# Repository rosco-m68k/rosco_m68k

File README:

# Motorola 68k single-board computer

This repository holds design files, firmware and software for my m68k 
single-board computer, AKA the Rosco_m68k.

You can find the project along with some logs about its development
on Hackaday: https://hackaday.io/project/164305-yet-another-m68k-homebrew

All released under the MIT licence. See LICENSE for details.

## Current design

Currently, the design for the system is:

* MC68010P10 at 8MHz, /DTACK grounded
* 16KB IO Space (0xF80000 - 0xFEFFFF)
* 16KB ROM (at 0xFC0000)
* 1MB RAM (0x0 - 0xFFFFF)
* TTL-based address decoding

In terms of software:

* Simple code in ROM to do various tests etc.
* Built with GCC and VASM

## Next steps

* Integrate MC68901 MFP
** This will provide timers, and a UART we can use to hook up a terminal. It also has some GPIOs and does interrupt handling (I already have the IC).
* Graphics - I'm thinking maybe Yamaha V9958 (assuming I can get hold of one)
** I would have liked to have used a Denise, but that would probably also require a (non-breadboard-friendly) Agnus.
** The datasheet and manual for the Denise probably aren't as easy to come by or complete, so there'd be more reverse-engineering.
* OS - Once the timers are available and I have some I/O capability, I want to build out the OS.
** Microkernel architecture (Similar in principle to Exec)
** Preemptive multitasking
** External storage (probably CF or SD in the first instance, though SD would require level shifting).

## Ideas for future enhancement

### Minimal memory protection

Extend address decoder to disallow access to certain locations based on 68k function pins.
E.g. in user mode:

	* Disallow ROM
	* Disallow IO
	* Disallow xKB at bottom of RAM (ExVecs and kernel heap)

The last one would make null dereferences generate a bus error.

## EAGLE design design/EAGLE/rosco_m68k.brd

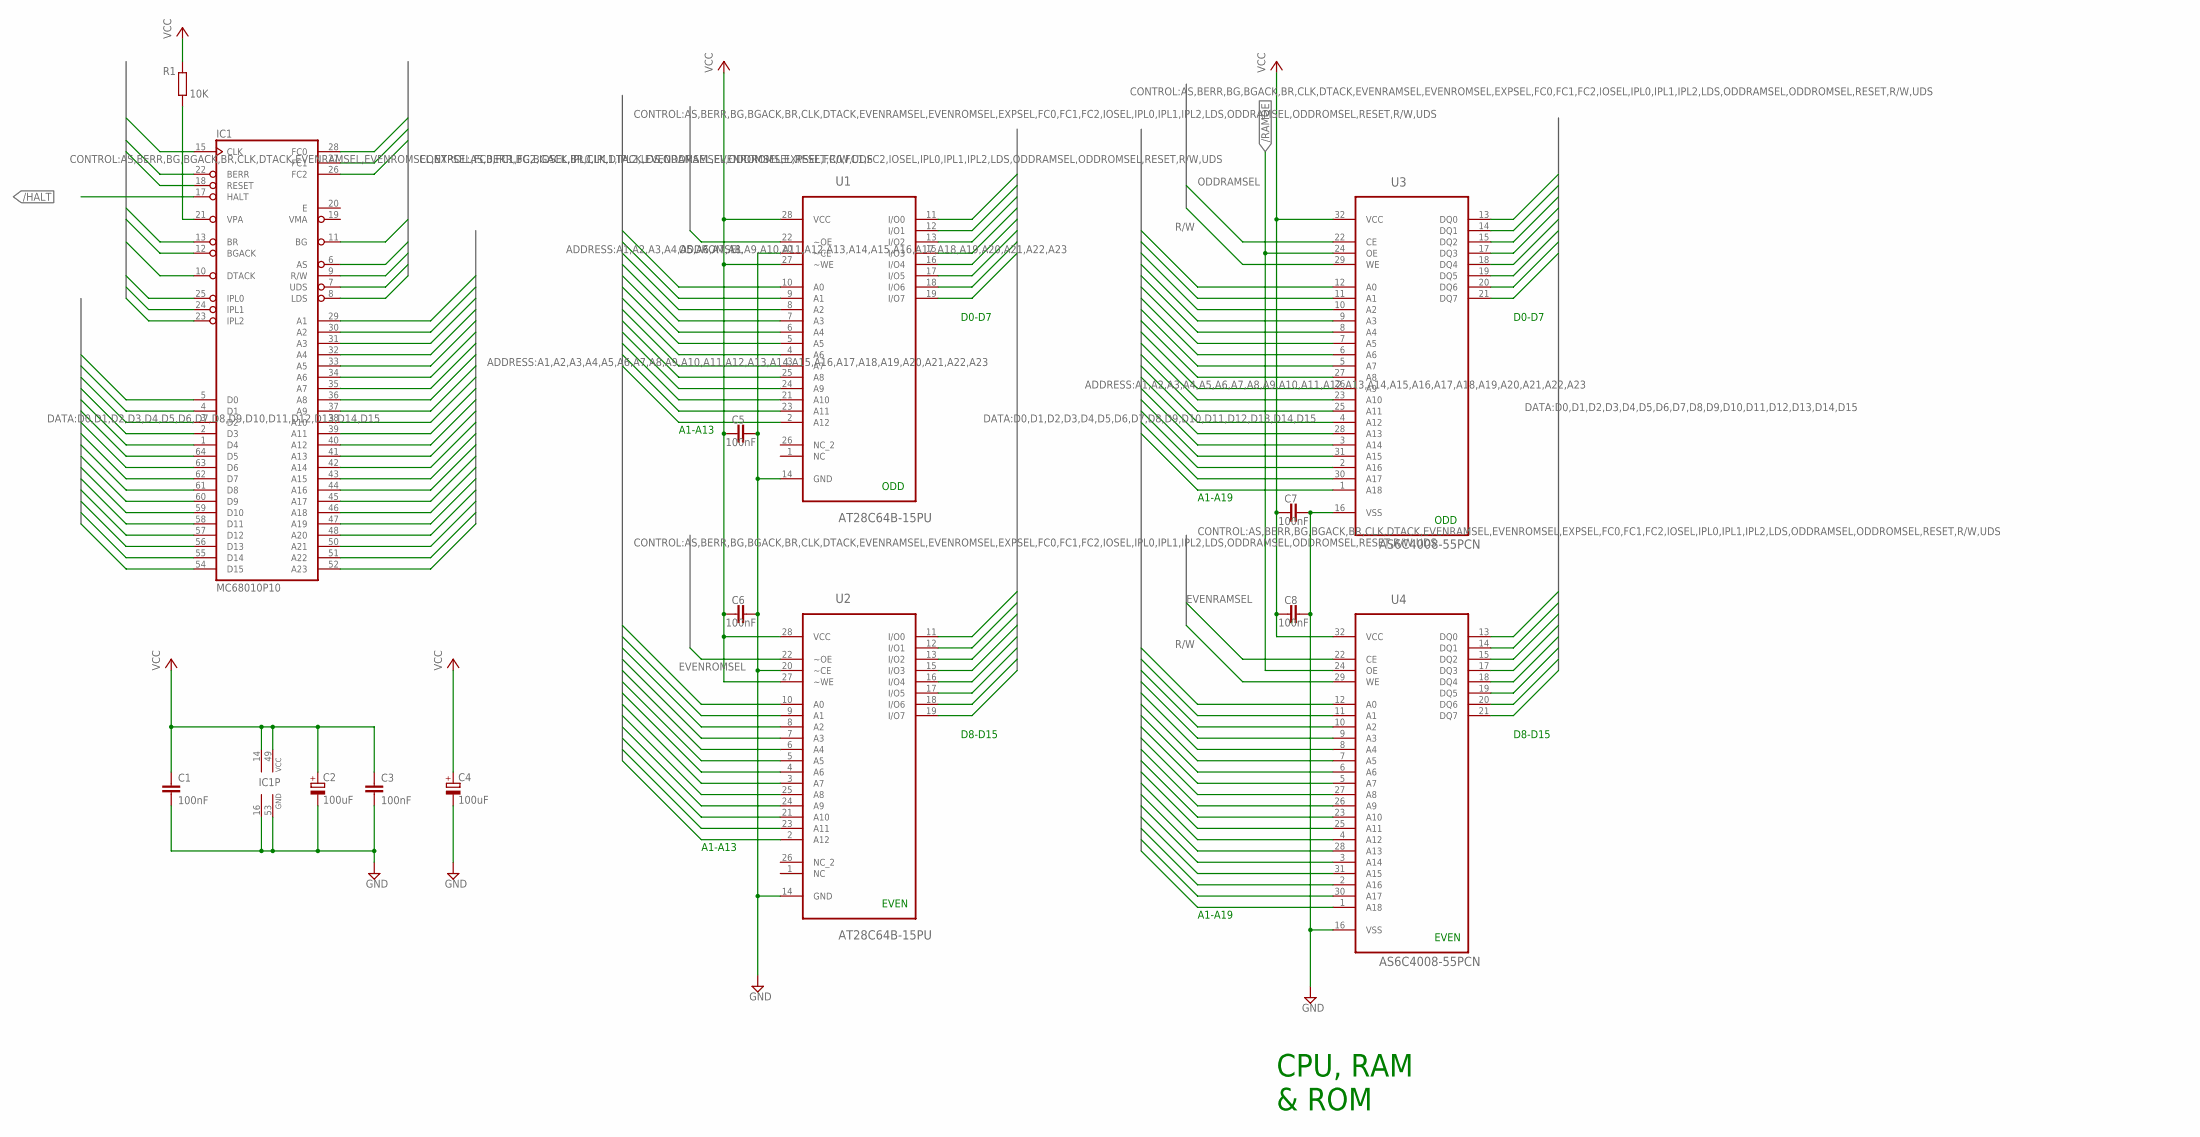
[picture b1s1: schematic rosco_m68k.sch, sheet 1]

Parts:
C1, C3, C5, C6, C7, C8: 100nF; C2.5-3
C2, C4: 100uF; E2,5-5
IC1: MC68010P10; DIL64
R1: 10K; 0207/10
U1, U2: AT28C64B-15PU; DIP254P1524X482-28
U3, U4: AS6C4008-55PCN; DIP254P1524X393-32

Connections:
/HALT: IC1.17 (HALT); also elsewhere on the board
/RAMOE: U3.24 (OE), U4.24 (OE); also elsewhere on the board
A1: IC1.29 (A1), U1.10 (A0), U2.10 (A0), U3.12 (A0), U4.12 (A0); also elsewhere on the board
A2: IC1.30 (A2), U1.9 (A1), U2.9 (A1), U3.11 (A1), U4.11 (A1); also elsewhere on the board
A3: IC1.31 (A3), U1.8 (A2), U2.8 (A2), U3.10 (A2), U4.10 (A2); also elsewhere on the board
A4: IC1.32 (A4), U1.7 (A3), U2.7 (A3), U3.9 (A3), U4.9 (A3); also elsewhere on the board
A5: IC1.33 (A5), U1.6 (A4), U2.6 (A4), U3.8 (A4), U4.8 (A4); also elsewhere on the board
A6: IC1.34 (A6), U1.5 (A5), U2.5 (A5), U3.7 (A5), U4.7 (A5); also elsewhere on the board
A7: IC1.35 (A7), U1.4 (A6), U2.4 (A6), U3.6 (A6), U4.6 (A6); also elsewhere on the board
A8: IC1.36 (A8), U1.3 (A7), U2.3 (A7), U3.5 (A7), U4.5 (A7); also elsewhere on the board
A9: IC1.37 (A9), U1.25 (A8), U2.25 (A8), U3.27 (A8), U4.27 (A8); also elsewhere on the board
A10: IC1.38 (A10), U1.24 (A9), U2.24 (A9), U3.26 (A9), U4.26 (A9); also elsewhere on the board
A11: IC1.39 (A11), U1.21 (A10), U2.21 (A10), U3.23 (A10), U4.23 (A10); also elsewhere on the board
A12: IC1.40 (A12), U1.23 (A11), U2.23 (A11), U3.25 (A11), U4.25 (A11); also elsewhere on the board
A13: IC1.41 (A13), U1.2 (A12), U2.2 (A12), U3.4 (A12), U4.4 (A12); also elsewhere on the board
A14: IC1.42 (A14), U3.28 (A13), U4.28 (A13); also elsewhere on the board
A15: IC1.43 (A15), U3.3 (A14), U4.3 (A14); also elsewhere on the board
A16: IC1.44 (A16), U3.31 (A15), U4.31 (A15); also elsewhere on the board
A17: IC1.45 (A17), U3.2 (A16), U4.2 (A16); also elsewhere on the board
A18: IC1.46 (A18), U3.30 (A17), U4.30 (A17); also elsewhere on the board
A19: IC1.47 (A19), U3.1 (A18), U4.1 (A18); also elsewhere on the board
A20: IC1.48 (A20); also elsewhere on the board
A21: IC1.50 (A21); also elsewhere on the board
A22: IC1.51 (A22); also elsewhere on the board
A23: IC1.52 (A23); also elsewhere on the board
AS: IC1.6 (AS); also elsewhere on the board
BERR: IC1.22 (BERR); also elsewhere on the board
BG: IC1.11 (BG); also elsewhere on the board
BGACK: IC1.12 (BGACK); also elsewhere on the board
BR: IC1.13 (BR); also elsewhere on the board
CLK: IC1.15 (CLK); also elsewhere on the board
D0: IC1.5 (D0), U1.11 (I/O0), U3.13 (DQ0); also elsewhere on the board
D1: IC1.4 (D1), U1.12 (I/O1), U3.14 (DQ1); also elsewhere on the board
D2: IC1.3 (D2), U1.13 (I/O2), U3.15 (DQ2); also elsewhere on the board
D3: IC1.2 (D3), U1.15 (I/O3), U3.17 (DQ3); also elsewhere on the board
D4: IC1.1 (D4), U1.16 (I/O4), U3.18 (DQ4); also elsewhere on the board
D5: IC1.64 (D5), U1.17 (I/O5), U3.19 (DQ5); also elsewhere on the board
D6: IC1.63 (D6), U1.18 (I/O6), U3.20 (DQ6); also elsewhere on the board
D7: IC1.62 (D7), U1.19 (I/O7), U3.21 (DQ7); also elsewhere on the board
D8: IC1.61 (D8), U2.11 (I/O0), U4.13 (DQ0); also elsewhere on the board
D9: IC1.60 (D9), U2.12 (I/O1), U4.14 (DQ1); also elsewhere on the board
D10: IC1.59 (D10), U2.13 (I/O2), U4.15 (DQ2); also elsewhere on the board
D11: IC1.58 (D11), U2.15 (I/O3), U4.17 (DQ3); also elsewhere on the board
D12: IC1.57 (D12), U2.16 (I/O4), U4.18 (DQ4); also elsewhere on the board
D13: IC1.56 (D13), U2.17 (I/O5), U4.19 (DQ5); also elsewhere on the board
D14: IC1.55 (D14), U2.18 (I/O6), U4.20 (DQ6); also elsewhere on the board
D15: IC1.54 (D15), U2.19 (I/O7), U4.21 (DQ7); also elsewhere on the board
DTACK: IC1.10 (DTACK); also elsewhere on the board
EVENRAMSEL: U4.22 (CE); also elsewhere on the board
EVENROMSEL: U2.22 (~OE); also elsewhere on the board
FC0: IC1.28 (FC0); also elsewhere on the board
FC1: IC1.27 (FC1); also elsewhere on the board
FC2: IC1.26 (FC2); also elsewhere on the board
GND: C1.2, C2.-, C3.2, C4.-, C5.2, C6.2, C7.2, C8.2, IC1.16 (GND), IC1.53 (GND), U1.14 (GND), U1.20 (~CE), U2.14 (GND), U2.20 (~CE), U3.16 (VSS), U4.16 (VSS); also elsewhere on the board
IPL0: IC1.25 (IPL0); also elsewhere on the board
IPL1: IC1.24 (IPL1); also elsewhere on the board
IPL2: IC1.23 (IPL2); also elsewhere on the board
LDS: IC1.8 (LDS); also elsewhere on the board
ODDRAMSEL: U3.22 (CE); also elsewhere on the board
ODDROMSEL: U1.22 (~OE); also elsewhere on the board
R/W: IC1.9 (R/W), U3.29 (WE), U4.29 (WE); also elsewhere on the board
RESET: IC1.18 (RESET); also elsewhere on the board
UDS: IC1.7 (UDS); also elsewhere on the board
VCC: C1.1, C2.+, C3.1, C4.+, C5.1, C6.1, C7.1, C8.1, IC1.14 (VCC), IC1.49 (VCC), R1.2, U1.27 (~WE), U1.28 (VCC), U2.27 (~WE), U2.28 (VCC), U3.32 (VCC), U4.32 (VCC); also elsewhere on the board
VPA: IC1.21 (VPA), R1.1

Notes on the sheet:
ODD
EVEN
D0-D7
D8-D15
A1-A13
A1-A19
CPU, RAM & ROM

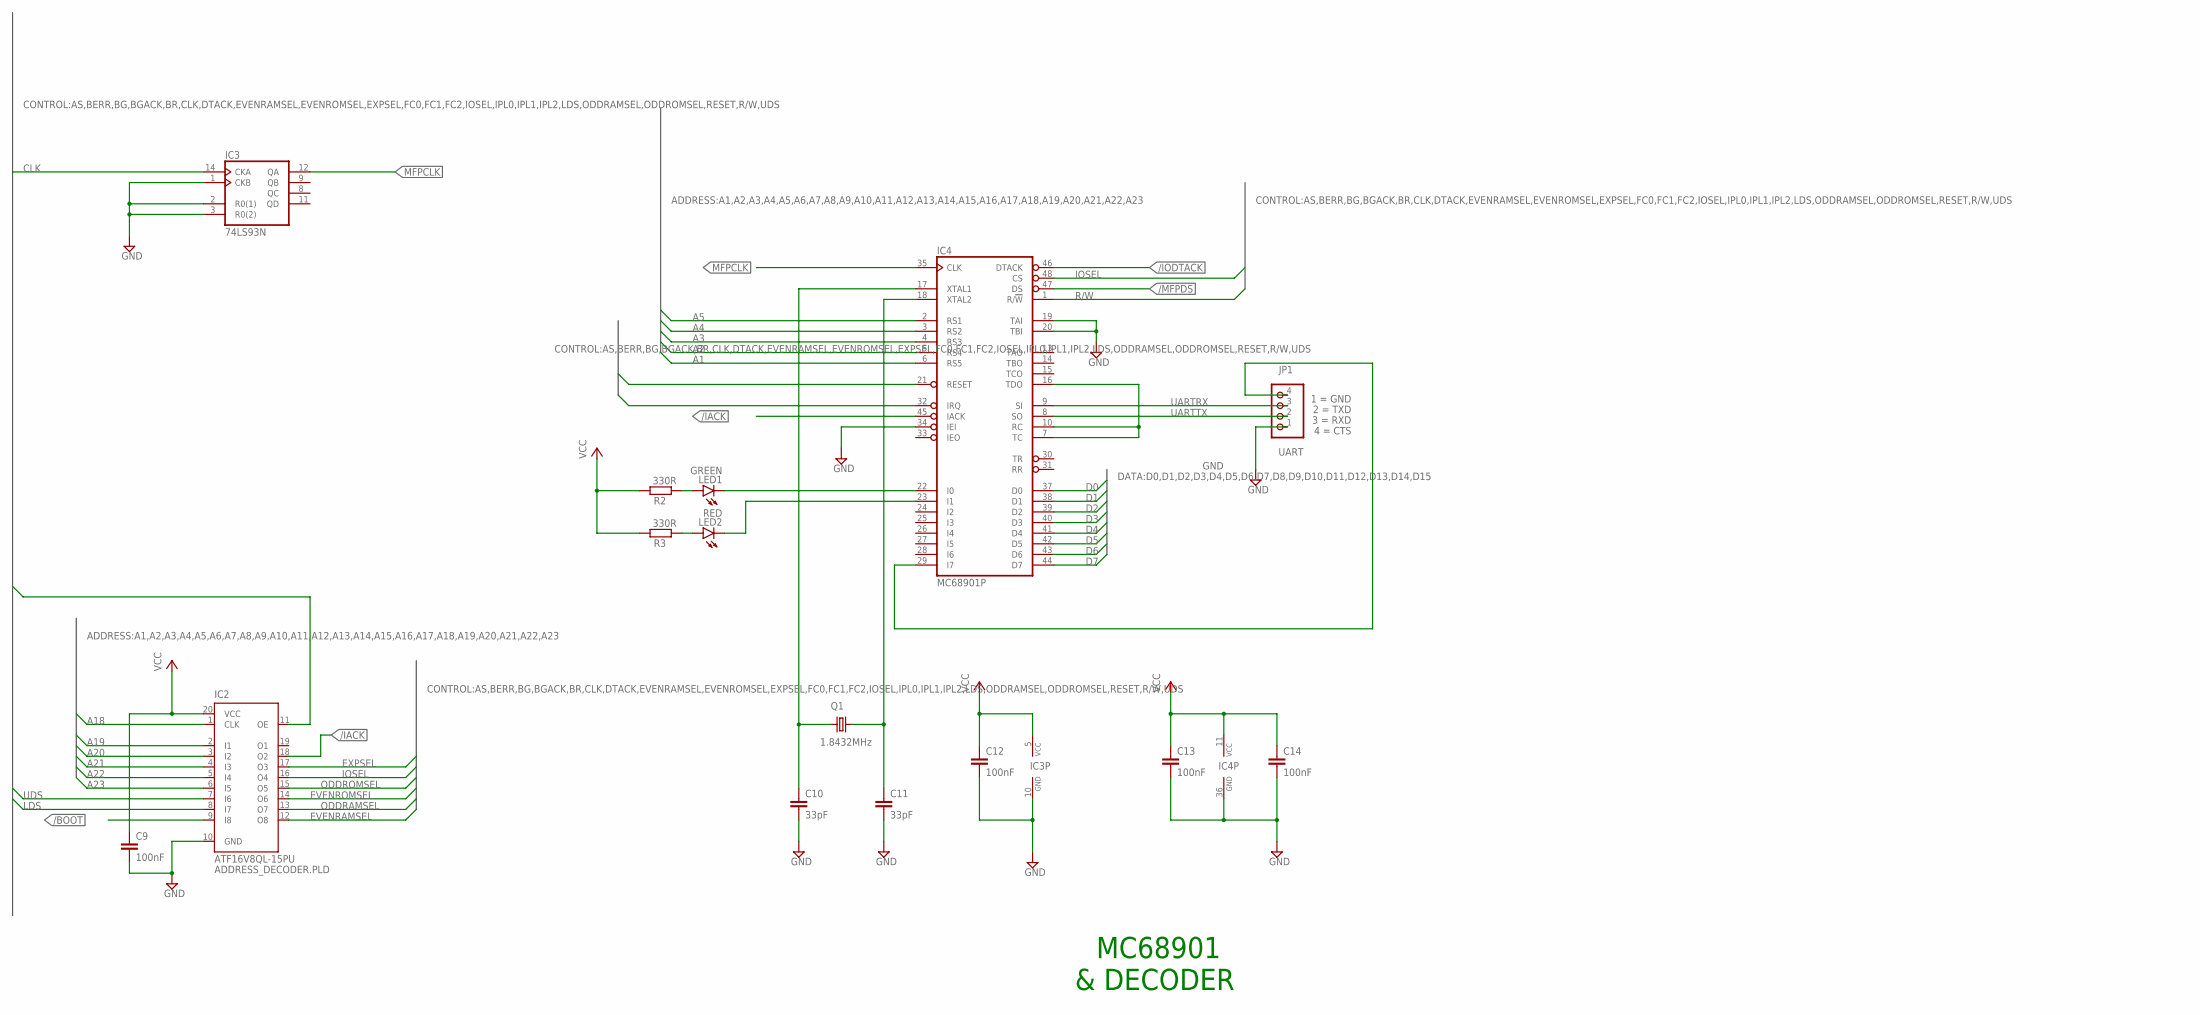
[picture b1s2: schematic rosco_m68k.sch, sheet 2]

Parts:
C9, C12, C13, C14: 100nF; C2.5-3
C10, C11: 33pF; C2.5-3
IC2: ATF16V8QL-15PU; DIL20; MPN ATF16V8QL-15PU
IC3: 74LS93N; DIL14
IC4: MC68901P; DIL48
JP1: UART; 1X04
LED1: GREEN; LED5MM
LED2: RED; LED5MM
Q1: 1.8432MHz; HC49/S
R2, R3: 330R; 0207/10

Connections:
/BOOT: IC2.9 (I8); also elsewhere on the board
/IACK: IC2.18 (O2), IC4.45 (IACK); also elsewhere on the board
/IODTACK: IC4.46 (DTACK); also elsewhere on the board
/MFPDS: IC4.47 (DS); also elsewhere on the board
A1: IC4.6 (RS5); also elsewhere on the board
A2: IC4.5 (RS4); also elsewhere on the board
A3: IC4.4 (RS3); also elsewhere on the board
A4: IC4.3 (RS2); also elsewhere on the board
A5: IC4.2 (RS1); also elsewhere on the board
A18: IC2.1 (CLK); also elsewhere on the board
A19: IC2.2 (I1); also elsewhere on the board
A20: IC2.3 (I2); also elsewhere on the board
A21: IC2.4 (I3); also elsewhere on the board
A22: IC2.5 (I4); also elsewhere on the board
A23: IC2.6 (I5); also elsewhere on the board
AS: IC2.11 (OE); also elsewhere on the board
CLK: IC3.14 (CKA); also elsewhere on the board
D0: IC4.37 (D0); also elsewhere on the board
D1: IC4.38 (D1); also elsewhere on the board
D2: IC4.39 (D2); also elsewhere on the board
D3: IC4.40 (D3); also elsewhere on the board
D4: IC4.41 (D4); also elsewhere on the board
D5: IC4.42 (D5); also elsewhere on the board
D6: IC4.43 (D6); also elsewhere on the board
D7: IC4.44 (D7); also elsewhere on the board
EVENRAMSEL: IC2.12 (O8); also elsewhere on the board
EVENROMSEL: IC2.14 (O6); also elsewhere on the board
EXPSEL: IC2.17 (O3); also elsewhere on the board
GND: C9.2, C10.2, C11.2, C12.2, C13.2, C14.2, IC2.10 (GND), IC3.1 (CKB), IC3.2 (R0(1)), IC3.3 (R0(2)), IC3.10 (GND), IC4.19 (TAI), IC4.20 (TBI), IC4.34 (IEI), IC4.36 (GND), JP1.1; also elsewhere on the board
IOSEL: IC2.16 (O4), IC4.48 (CS); also elsewhere on the board
IPL2: IC4.32 (IRQ); also elsewhere on the board
LDS: IC2.8 (I7); also elsewhere on the board
MFPCLK: IC3.12 (QA), IC4.35 (CLK)
MFPIO0: IC4.22 (I0), LED1.K (C)
MFPIO1: IC4.23 (I1), LED2.K (C)
MFPXTAL1: C10.1, IC4.17 (XTAL1), Q1.1
MFPXTAL2: C11.1, IC4.18 (XTAL2), Q1.2
unnamed: LED2.A, R3.1
unnamed: LED1.A, R2.1
ODDRAMSEL: IC2.13 (O7); also elsewhere on the board
ODDROMSEL: IC2.15 (O5); also elsewhere on the board
R/W: IC4.1 (R/!W); also elsewhere on the board
RESET: IC4.21 (RESET); also elsewhere on the board
UARTCLK: IC4.7 (TC), IC4.10 (RC), IC4.16 (TDO)
UARTCTS: IC4.29 (I7), JP1.4
UARTRX: IC4.9 (SI), JP1.3
UARTTX: IC4.8 (SO), JP1.2
UDS: IC2.7 (I6); also elsewhere on the board
VCC: C9.1, C12.1, C13.1, C14.1, IC2.20 (VCC), IC3.5 (VCC), IC4.11 (VCC), R2.2, R3.2; also elsewhere on the board

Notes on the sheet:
MC68901
& DECODER

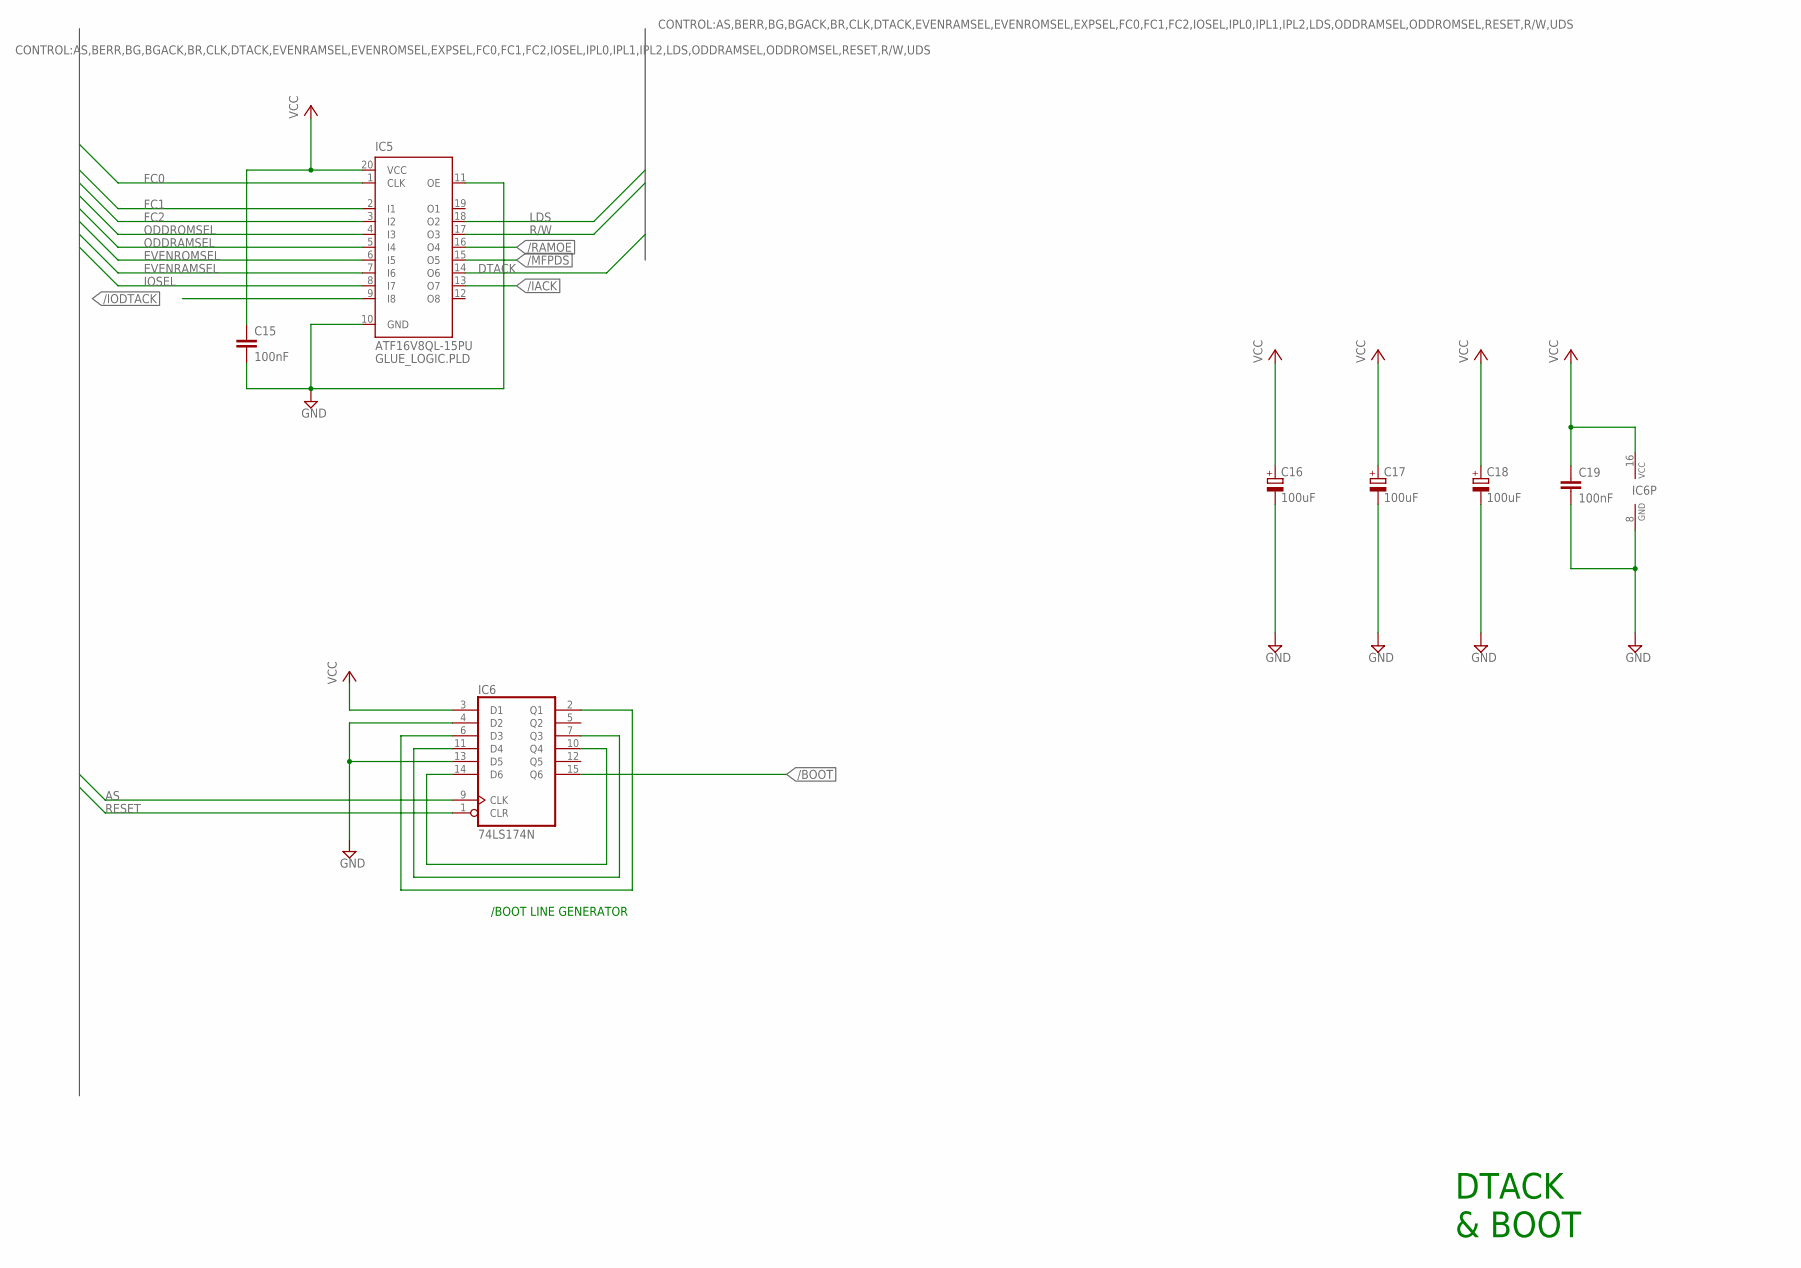
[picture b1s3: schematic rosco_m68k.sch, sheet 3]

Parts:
C15, C19: 100nF; C2.5-3
C16, C17, C18: 100uF; E2,5-5
IC5: ATF16V8QL-15PU; DIL20; MPN ATF16V8QL-15PU
IC6: 74LS174N; DIL16

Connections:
/BOOT: IC6.15 (Q6); also elsewhere on the board
/IACK: IC5.13 (O7); also elsewhere on the board
/IODTACK: IC5.9 (I8); also elsewhere on the board
/MFPDS: IC5.15 (O5); also elsewhere on the board
/RAMOE: IC5.16 (O4); also elsewhere on the board
AS: IC6.9 (CLK); also elsewhere on the board
DTACK: IC5.14 (O6); also elsewhere on the board
EVENRAMSEL: IC5.7 (I6); also elsewhere on the board
EVENROMSEL: IC5.6 (I5); also elsewhere on the board
FC0: IC5.1 (CLK); also elsewhere on the board
FC1: IC5.2 (I1); also elsewhere on the board
FC2: IC5.3 (I2); also elsewhere on the board
GND: C15.2, C16.-, C17.-, C18.-, C19.2, IC5.10 (GND), IC5.11 (OE), IC6.4 (D2), IC6.8 (GND), IC6.13 (D5); also elsewhere on the board
IOSEL: IC5.8 (I7); also elsewhere on the board
LDS: IC5.18 (O2); also elsewhere on the board
unnamed: IC6.7 (Q3), IC6.11 (D4)
unnamed: IC6.10 (Q4), IC6.14 (D6)
unnamed: IC6.2 (Q1), IC6.6 (D3)
ODDRAMSEL: IC5.5 (I4); also elsewhere on the board
ODDROMSEL: IC5.4 (I3); also elsewhere on the board
R/W: IC5.17 (O3); also elsewhere on the board
RESET: IC6.1 (CLR); also elsewhere on the board
VCC: C15.1, C16.+, C17.+, C18.+, C19.1, IC5.20 (VCC), IC6.3 (D1), IC6.16 (VCC); also elsewhere on the board

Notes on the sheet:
/BOOT LINE GENERATOR
DTACK & BOOT

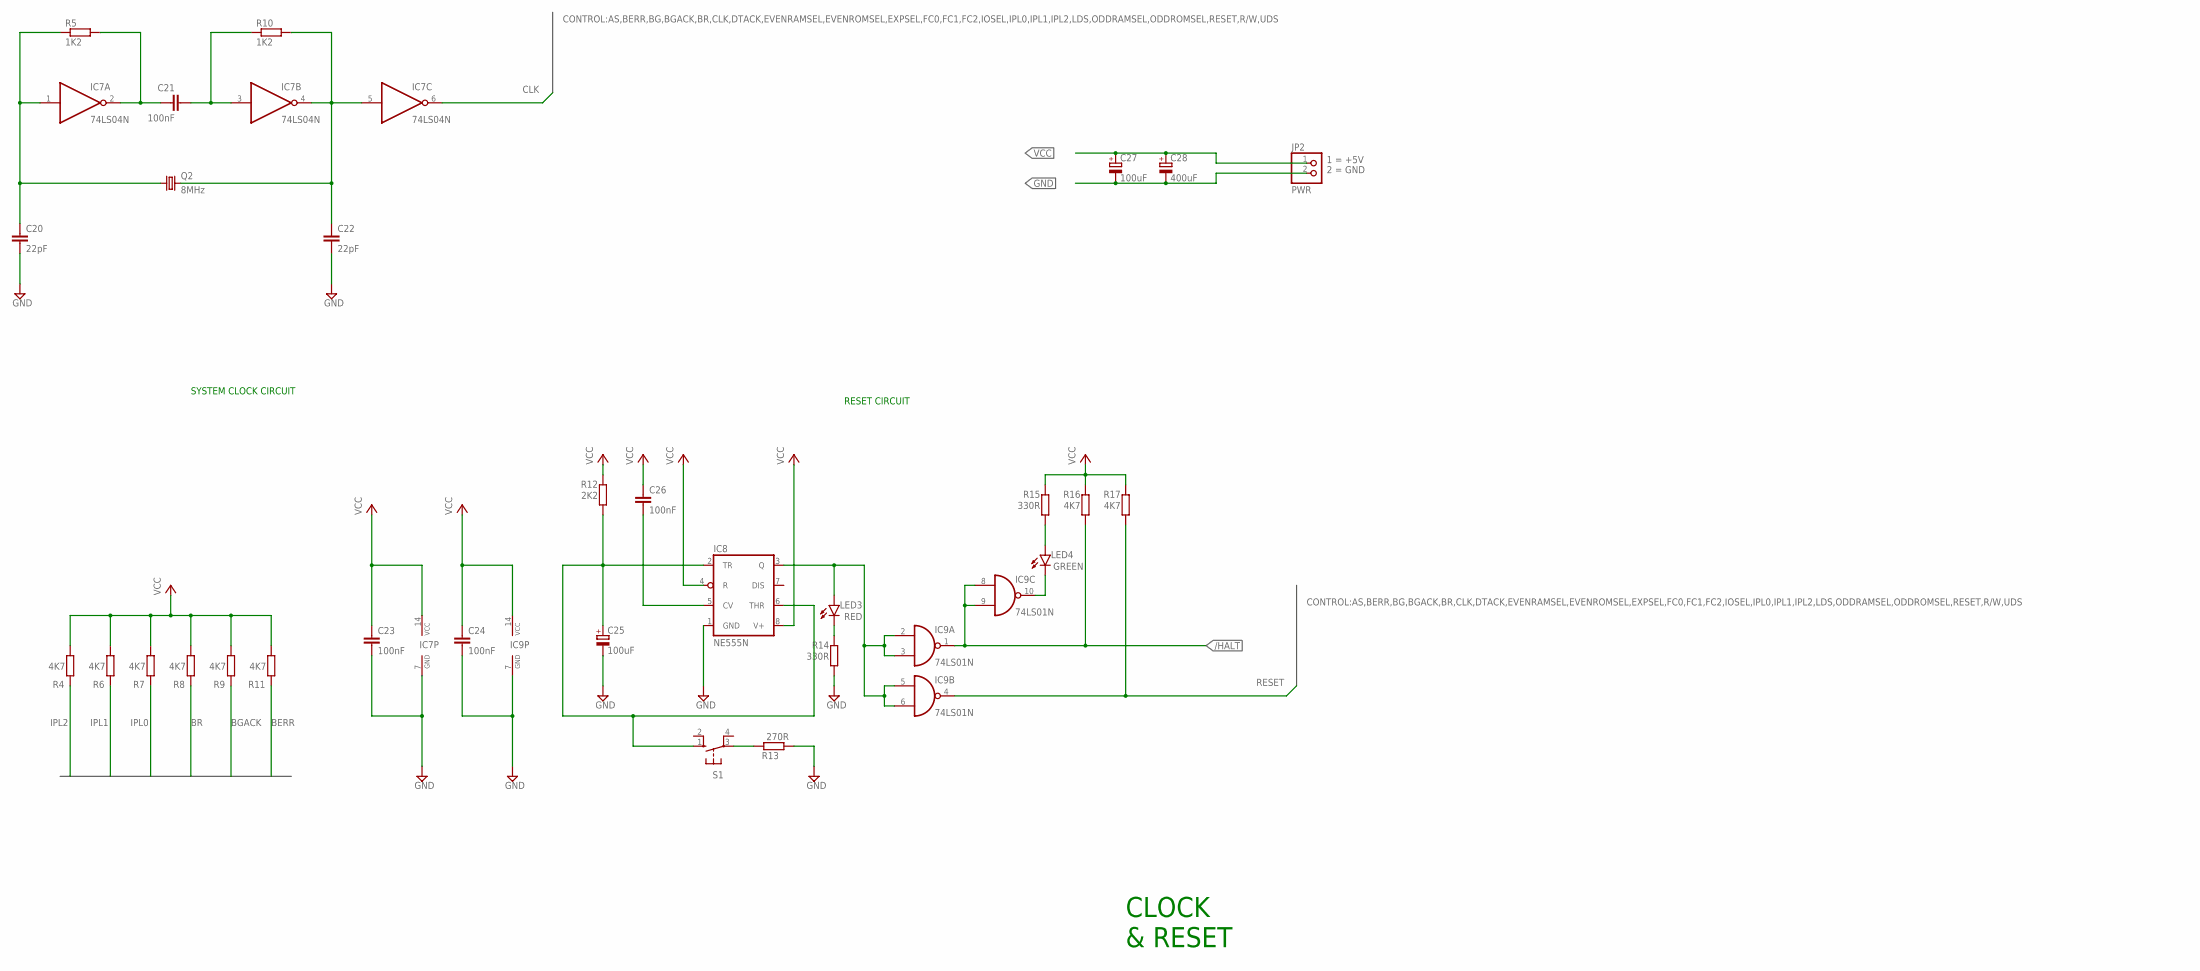
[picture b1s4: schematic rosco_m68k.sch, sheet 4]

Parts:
C20, C22: 22pF; C2.5-3
C21, C23, C24, C26: 100nF; C2.5-3
C25, C27: 100uF; E2,5-5
C28: 400uF; E3,5-10
IC7: 74LS04N; DIL14
IC8: NE555N; DIL08
IC9: 74LS01N; DIL14
JP2: PWR; 1X02
LED3: RED; LED5MM
LED4: GREEN; LED5MM
Q2: 8MHz; HC49/S
R4, R6, R7, R8, R9, R11, R16, R17: 4K7; 0207/10
R5, R10: 1K2; 0207/10
R12: 2K2; 0207/10
R13: 270R; 0207/10
R14, R15: 330R; 0207/10
S1: 10-XX; B3F-10XX

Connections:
/HALT: IC9.1 (O), IC9.8 (I0), IC9.9 (I1), R16.1; also elsewhere on the board
BERR: R11.1; also elsewhere on the board
BGACK: R9.1; also elsewhere on the board
BR: R8.1; also elsewhere on the board
CLK: IC7.6 (O); also elsewhere on the board
GND: C20.2, C22.2, C23.2, C24.2, C25.-, C27.-, C28.-, IC7.7 (GND), IC8.1 (GND), IC9.7 (GND), JP2.2, R13.1, R14.1; also elsewhere on the board
IPL0: R7.1; also elsewhere on the board
IPL1: R6.1; also elsewhere on the board
IPL2: R4.1; also elsewhere on the board
unnamed: C21.1, IC7.2 (O), R5.2
unnamed: C21.2, IC7.3 (I), R10.1
unnamed: C22.1, IC7.4 (O), IC7.5 (I), Q2.2, R10.2
unnamed: C20.1, IC7.1 (I), Q2.1, R5.1
unnamed: C26.2, IC8.5 (CV)
unnamed: LED3.K (C), R14.2
unnamed: IC9.10 (O), LED4.K (C)
unnamed: LED4.A, R15.1
unnamed: IC8.3 (Q), IC9.2 (I0), IC9.3 (I1), IC9.5 (I0), IC9.6 (I1), LED3.A
unnamed: R13.2, S1.3
unnamed: C25.+, IC8.2 (TR), IC8.6 (THR), R12.1, S1.1 (S)
RESET: IC9.4 (O), R17.1; also elsewhere on the board
VCC: C23.1, C24.1, C26.1, C27.+, C28.+, IC7.14 (VCC), IC8.4 (R), IC8.8 (V+), IC9.14 (VCC), JP2.1, R4.2, R6.2, R7.2, R8.2, R9.2, R11.2, R12.2, R15.2, R16.2, R17.2; also elsewhere on the board

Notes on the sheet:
RESET CIRCUIT
SYSTEM CLOCK CIRCUIT
CLOCK & RESET

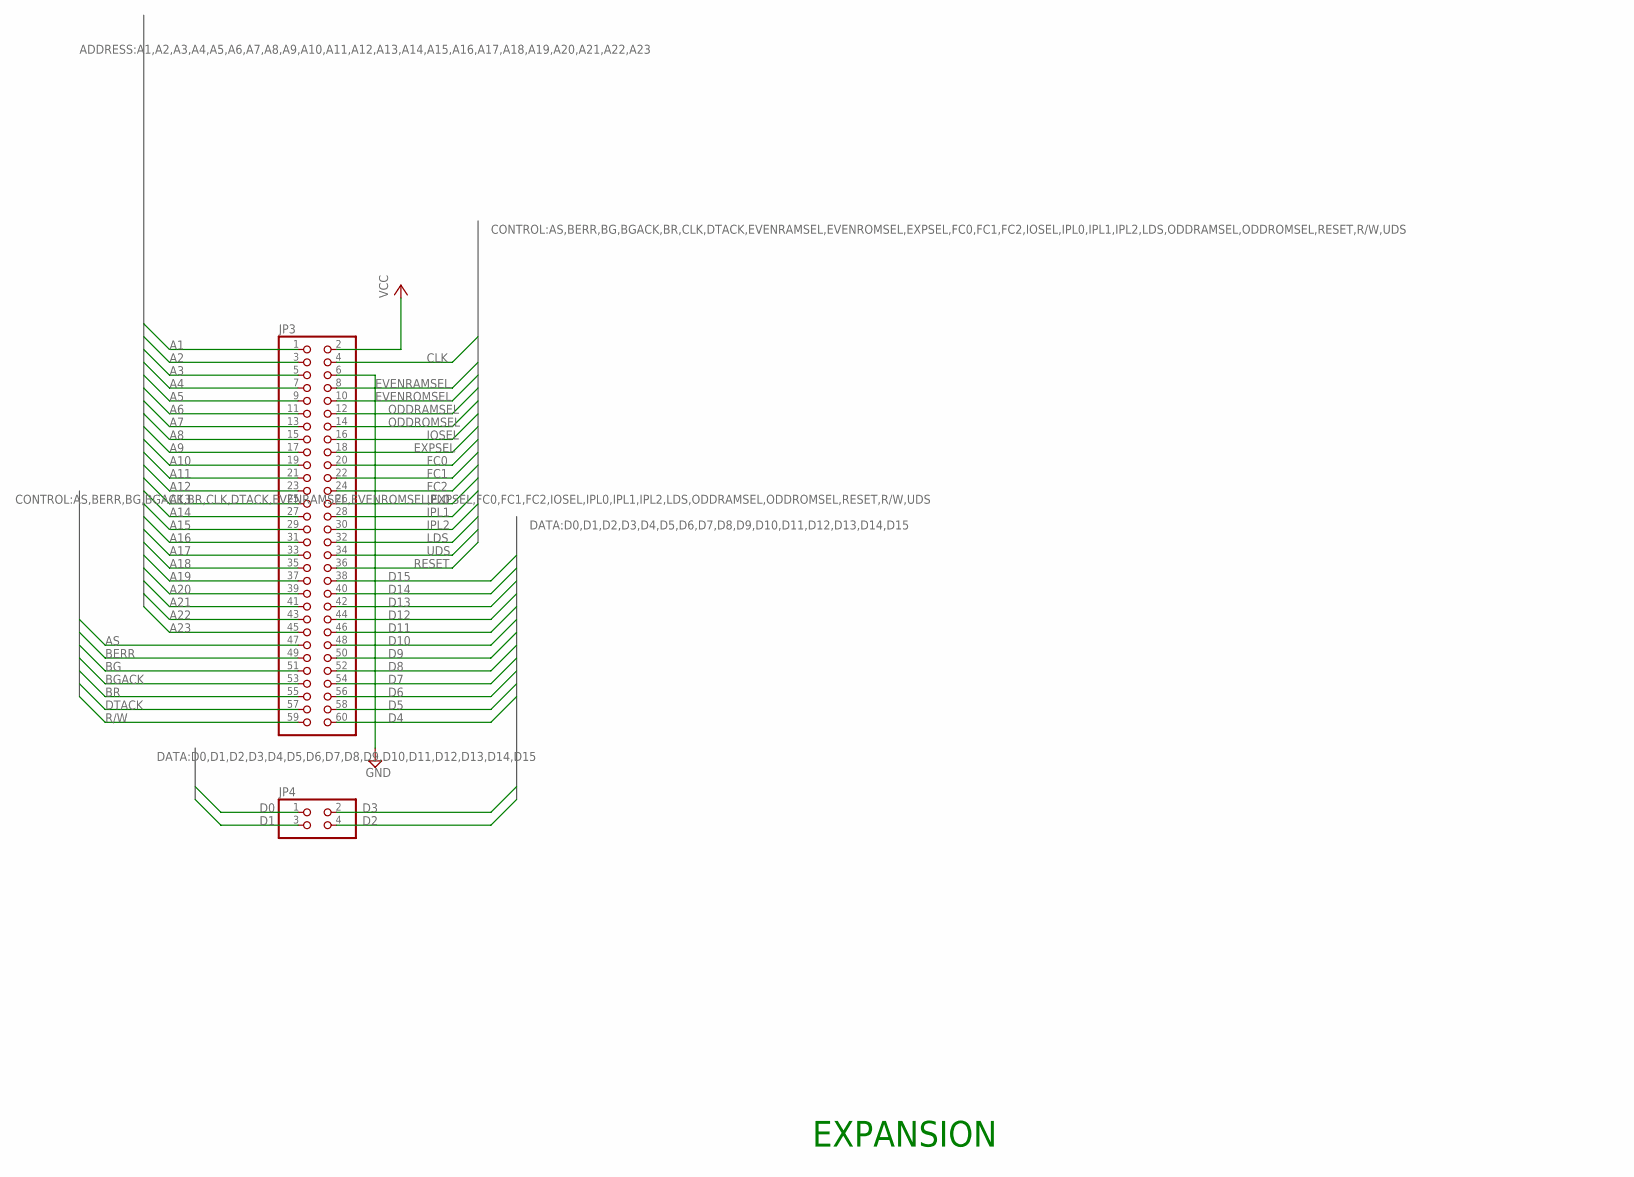
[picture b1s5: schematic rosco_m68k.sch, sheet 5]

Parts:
JP3: PINHD-2X30; 2X30
JP4: PINHD-2X2; 2X02

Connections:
A1: JP3.1; also elsewhere on the board
A2: JP3.3; also elsewhere on the board
A3: JP3.5; also elsewhere on the board
A4: JP3.7; also elsewhere on the board
A5: JP3.9; also elsewhere on the board
A6: JP3.11; also elsewhere on the board
A7: JP3.13; also elsewhere on the board
A8: JP3.15; also elsewhere on the board
A9: JP3.17; also elsewhere on the board
A10: JP3.19; also elsewhere on the board
A11: JP3.21; also elsewhere on the board
A12: JP3.23; also elsewhere on the board
A13: JP3.25; also elsewhere on the board
A14: JP3.27; also elsewhere on the board
A15: JP3.29; also elsewhere on the board
A16: JP3.31; also elsewhere on the board
A17: JP3.33; also elsewhere on the board
A18: JP3.35; also elsewhere on the board
A19: JP3.37; also elsewhere on the board
A20: JP3.39; also elsewhere on the board
A21: JP3.41; also elsewhere on the board
A22: JP3.43; also elsewhere on the board
A23: JP3.45; also elsewhere on the board
AS: JP3.47; also elsewhere on the board
BERR: JP3.49; also elsewhere on the board
BG: JP3.51; also elsewhere on the board
BGACK: JP3.53; also elsewhere on the board
BR: JP3.55; also elsewhere on the board
CLK: JP3.4; also elsewhere on the board
D0: JP4.1; also elsewhere on the board
D1: JP4.3; also elsewhere on the board
D2: JP4.4; also elsewhere on the board
D3: JP4.2; also elsewhere on the board
D4: JP3.60; also elsewhere on the board
D5: JP3.58; also elsewhere on the board
D6: JP3.56; also elsewhere on the board
D7: JP3.54; also elsewhere on the board
D8: JP3.52; also elsewhere on the board
D9: JP3.50; also elsewhere on the board
D10: JP3.48; also elsewhere on the board
D11: JP3.46; also elsewhere on the board
D12: JP3.44; also elsewhere on the board
D13: JP3.42; also elsewhere on the board
D14: JP3.40; also elsewhere on the board
D15: JP3.38; also elsewhere on the board
DTACK: JP3.57; also elsewhere on the board
EVENRAMSEL: JP3.8; also elsewhere on the board
EVENROMSEL: JP3.10; also elsewhere on the board
EXPSEL: JP3.18; also elsewhere on the board
FC0: JP3.20; also elsewhere on the board
FC1: JP3.22; also elsewhere on the board
FC2: JP3.24; also elsewhere on the board
GND: JP3.6; also elsewhere on the board
IOSEL: JP3.16; also elsewhere on the board
IPL0: JP3.26; also elsewhere on the board
IPL1: JP3.28; also elsewhere on the board
IPL2: JP3.30; also elsewhere on the board
LDS: JP3.32; also elsewhere on the board
ODDRAMSEL: JP3.12; also elsewhere on the board
ODDROMSEL: JP3.14; also elsewhere on the board
R/W: JP3.59; also elsewhere on the board
RESET: JP3.36; also elsewhere on the board
UDS: JP3.34; also elsewhere on the board
VCC: JP3.2; also elsewhere on the board

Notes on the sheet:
EXPANSION

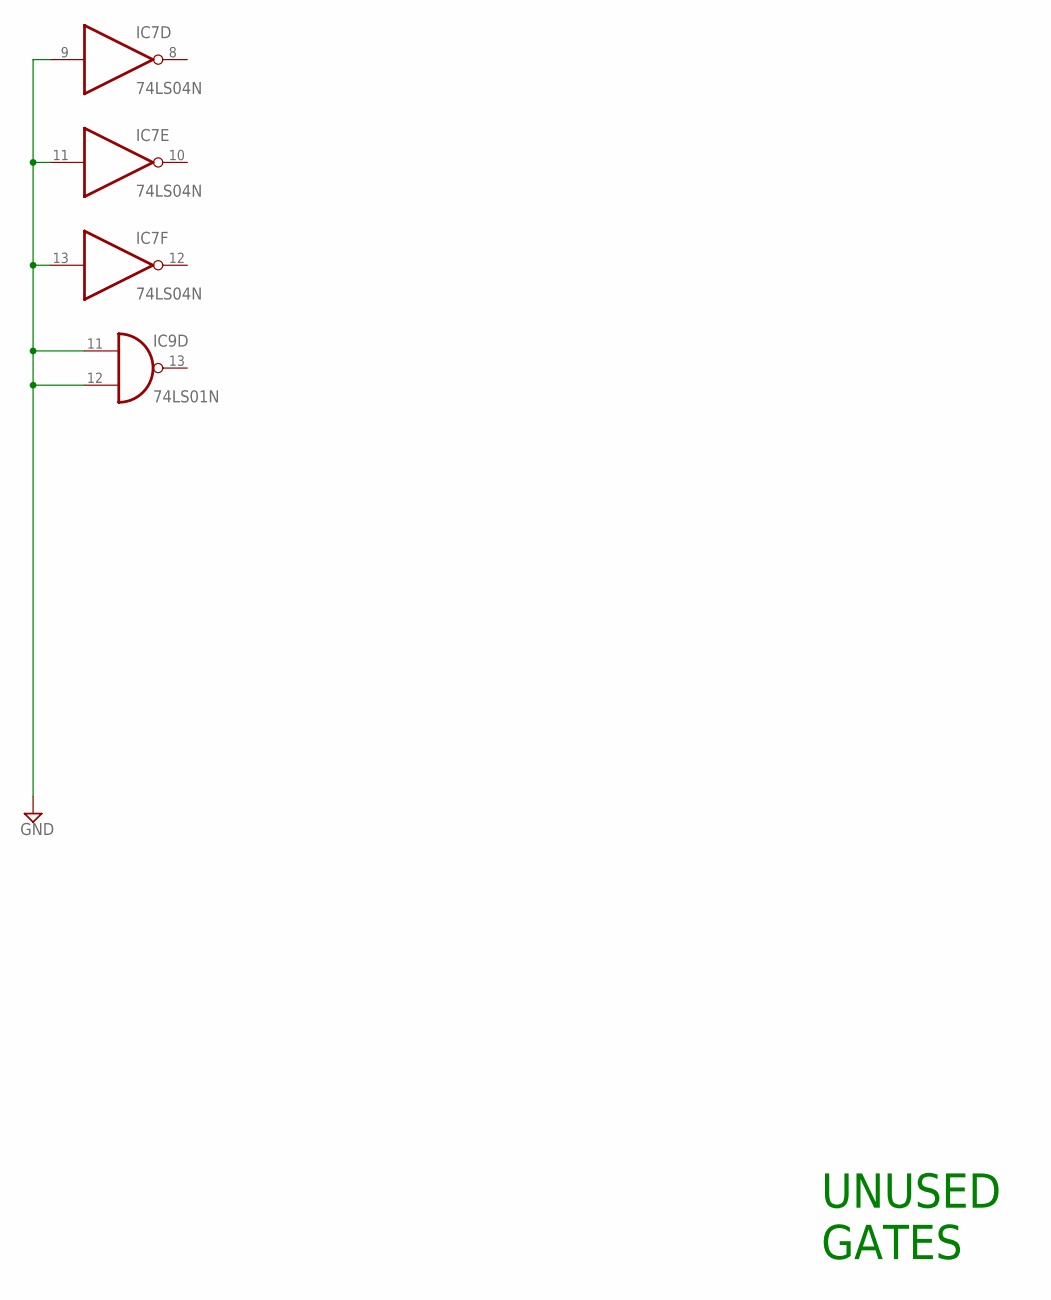
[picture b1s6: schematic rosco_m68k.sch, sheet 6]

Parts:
IC7: 74LS04N; DIL14
IC9: 74LS01N; DIL14

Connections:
GND: IC7.9 (I), IC7.11 (I), IC7.13 (I), IC9.11 (I0), IC9.12 (I1); also elsewhere on the board

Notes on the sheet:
UNUSED GATES

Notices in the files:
design/EAGLE/rosco_m68k.brd:
copyright 2019
